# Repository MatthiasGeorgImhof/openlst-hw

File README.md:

$1K CubeSat Design
==========================

This forked repo adapts the hardware from the OpenLST Reference into something that works for my $1K CubeSat project

**Please note that this repository is desgined to be used as a submodule**, since it depends on symbols & footprints in my [1KCubeSat_Hardware repository](https://github.com/rgw3d/1KCubeSat_Hardware)

Overview
--------

This is an iteration on the OpenLST CC1110 based design, which itself is a simplified version of the TI CC1110 432 MHz reference design.
While the CC1110 can operate over 400-470MHz, this board is designed to operate around 435MHz, within the 435MHz-438MHz US Amateur radio band.
See the [FCC's chart, specifically section 5.282](https://transition.fcc.gov/oet/spectrum/table/fcctable.pdf)

* [Schematic](pdf/openlst-hw.pdf) in PDF form
* [Bill of materials](bom/) with ordering information & datasheet links
* [Gerber files](gerber/osh_park) for PCB fabrication

RF Pipeline
-----------

* **0433BM15A0001 Balun**. Designed for 430-435MHz, but should work up to 437MHz. Single part, designed specifically for the CC1110. I did not want to design my own balun.
* **PE4250MLI RF Switch**. Generic SPDT RF Switch. First RF switch breaks out to a test port. Second RF switch switches between TX & RX paths on the RF Frontend (RFFM6403).
* **RFFM6403 Analog Frontend**. TX path with 1.5W PA, RX path with LNA & SAW filter. Designed to work over the 408-455MHz band.
* **SF2446E SAW Filter**. Part of the Analog Frontend RX path. 430-440MHz band pass.
* 50 Ohm
* Impedance calculations for OSH Park PCB found [here](images/osh-park-4-layer-50ohms.png)

Pictures
--------

Original README below

OpenLST Reference Hardware
==========================

This repository contains a KiCad project with a hardware reference
implementation for the OpenLST.  This design is a simplified version
of the Texas Instruments CC1110 432 MHz reference design.  A 1 watt
power amplifier module has been added to increase operating range.
The design is intended for use at 437 MHz, however, it may be modified
for use at other frequencies.

The user is responsible for obtaining and maintaining the necessary
license to operate this radio.  The example project uses frequencies
in the US Amateur Radio UHF band. Transmissions in this band require a
valid FCC license and compliance with CFR Part 97.

License & Legal Information
---------------------------

Copyright 2018 Planet Labs Inc. This work is licensed under a
Creative Commons Attribution-ShareAlike 4.0 International License.

This document may contain technology or software the export of which
is or may be restricted by the Export Administration Act and the
Export Administration Regulations (EAR), 15 C.F.R. parts
730-774. Diversion contrary to U.S. law is prohibited.

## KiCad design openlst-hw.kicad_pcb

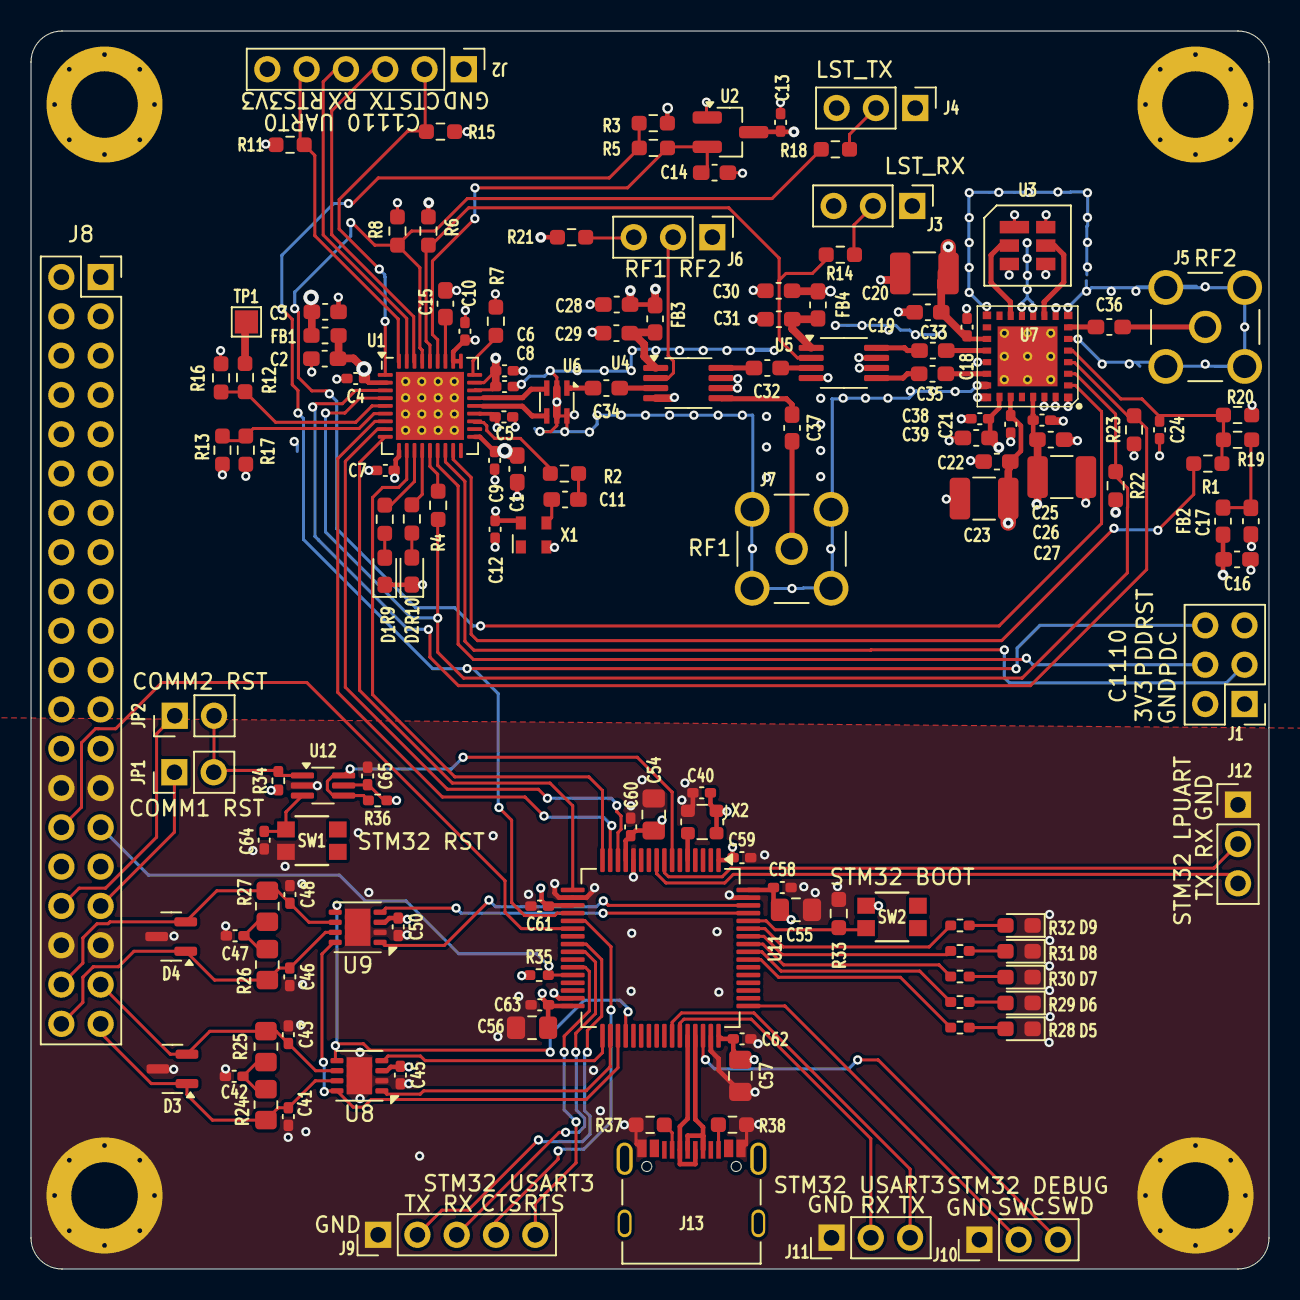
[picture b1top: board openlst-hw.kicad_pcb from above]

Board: 4 copper layers, 80.0 x 80.0 mm, 146 parts (0 on the bottom side), 104 nets.

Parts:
C1, C19, C22, C26, C39: 10u; C_0603_1608Metric_Pad1.08x0.95mm_HandSolder
C2, C3, C15, C16, C17, C28, C29, C30, C31: 1u; C_0603_1608Metric_Pad1.08x0.95mm_HandSolder
C4, C5, C6, C7, C8, C9, C10, C12, C13, C18, C21, C24, C25, C38, C40, C45, C50, C58, C59, C60, C61, C62, C63, C64, C65: 100n; C_0402_1005Metric_Pad0.74x0.62mm_HandSolder
C11, C14: 10n; C_0603_1608Metric_Pad1.08x0.95mm_HandSolder
C20, C23, C27: 47u; C_1210_3225Metric_Pad1.33x2.70mm_HandSolder
C32, C33, C34, C35, C36, C37: 220p; C_0603_1608Metric_Pad1.08x0.95mm_HandSolder
C41, C43, C46, C48: 100p; C_0402_1005Metric_Pad0.74x0.62mm_HandSolder
C42, C47: 4.7n; C_0402_1005Metric_Pad0.74x0.62mm_HandSolder
C54, C55, C56, C57: 10u; C_0805_2012Metric_Pad1.18x1.45mm_HandSolder
D1, D2: ORANGE; LED_0603_1608Metric_Pad1.05x0.95mm_HandSolder
D3, D4: NUP2105L; SOT-23
D5: LED_SMD_RED; LED_0603_1608Metric_Pad1.05x0.95mm_HandSolder
D6: LED_SMD_GREEN; LED_0603_1608Metric_Pad1.05x0.95mm_HandSolder
D7, D8, D9: LED_SMD_YELLOW; LED_0603_1608Metric_Pad1.05x0.95mm_HandSolder
FB1, FB2, FB3, FB4: Z=1k @ 100M; L_0603_1608Metric_Pad1.05x0.95mm_HandSolder
H1, H2, H3, H4: MountingHole_Pad; MountingHole_4.3mm_M4_Pad_Via_Custom
J1: CC Prog/Debug; PinHeader_2x03_P2.54mm_Vertical
J2: UART0; PinHeader_1x06_P2.54mm_Vertical
J3, J4: Control Outputs; PinHeader_1x03_P2.54mm_Vertical
J5: ANT; LINX_CONSMA001-G
J6: Switch Select; PinHeader_1x03_P2.54mm_Vertical
J7: Conn_Coaxial; LINX_CONSMA001-G
J8: PC104 Conn_02x20_Odd_Even; PinSocket_2x20_P2.54mm_Vertical
J9: Conn_01x05_Pin; PinHeader_1x05_P2.54mm_Vertical
J10, J11, J12: Conn_01x03_Pin; PinHeader_1x03_P2.54mm_Vertical
J13: 10155435-00011LF; AMPHENOL_10155435-00011LF
JP1, JP2: Jumper_2_Open; PinHeader_1x02_P2.54mm_Vertical
R1, R2, R4: 0; R_0603_1608Metric_Pad0.98x0.95mm_HandSolder
R3, R17: 47K; R_0603_1608Metric_Pad0.98x0.95mm_HandSolder
R5, R6, R8, R22, R23: 1K; R_0603_1608Metric_Pad0.98x0.95mm_HandSolder
R7: 56K; R_0603_1608Metric_Pad0.98x0.95mm_HandSolder
R9, R10: 680; R_0603_1608Metric_Pad0.98x0.95mm_HandSolder
R11, R15: 100K; R_0603_1608Metric_Pad0.98x0.95mm_HandSolder
R12, R16: DNP; R_0603_1608Metric_Pad0.98x0.95mm_HandSolder
R13, R21: 20K; R_0603_1608Metric_Pad0.98x0.95mm_HandSolder
R14, R18: 22; R_0603_1608Metric_Pad0.98x0.95mm_HandSolder
R19: 3.09K; R_0603_1608Metric_Pad0.98x0.95mm_HandSolder
R20: 6.65K; R_0603_1608Metric_Pad0.98x0.95mm_HandSolder
R24, R25, R26, R27: 60R4; R_0805_2012Metric_Pad1.20x1.40mm_HandSolder
R28, R29, R30, R31, R32: 680; R_0402_1005Metric_Pad0.72x0.64mm_HandSolder
R33: 10k; R_0603_1608Metric_Pad0.98x0.95mm_HandSolder
R34, R35, R36: 100K; R_0402_1005Metric_Pad0.72x0.64mm_HandSolder
R37, R38: 5K1; R_0603_1608Metric_Pad0.98x0.95mm_HandSolder
SW1, SW2: EVP-AA602W; EVP602AA
TP1: TestPoint; TestPoint_Pad_1.5x1.5mm
U1: CC1110; Texas_RHH0036C_VQFN-36-1EP_6x6mm_P0.5mm_EP4.4x4.4mm_Thermal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
U2: MIC803; SOT-23_Handsoldering
U3: SF2446E
U4, U5: PE4250MLI; MSOP-8_3x3mm_P0.65mm
U6: 0433BM15A0001; Balun_Johanson_0896BM15A0001
U7: RFFM6406
U8, U9: TCAN3414; VSON-8-1EP_3x3mm_P0.65mm_EP1.65x2.4mm
U11: STM32L496RGTx; LQFP-64_10x10mm_P0.5mm
U12: 74LVC2G07; SOT-363_SC-70-6_Handsoldering
X1: 27MHz; Oscillator_SMD_Abracon_ASDMB-4Pin_2.5x2.0mm
X2: 10MHz; Oscillator_SMD_ECS_2520MV-xxx-xx-4Pin_2.5x2.0mm

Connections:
/CAN Bridge/ATTENTION: J8.29, R35.2, U11.28 (PB2)
/CAN Bridge/CAN1_H: C46.1, D4.1 (K), J8.40, R26.1, U9.7 (CANH)
/CAN Bridge/CAN1_L: C48.2, D4.2 (K), J8.38, R27.2, U9.6 (CANL)
/CAN Bridge/CAN2_H: C41.1, D3.1 (K), J8.39, R24.1, U8.7 (CANH)
/CAN Bridge/CAN2_L: C43.2, D3.2 (K), J8.37, R25.2, U8.6 (CANL)
/CAN Bridge/CAN Transceiver1/CAN_RX: U9.4 (RXD), U11.61 (PB8)
/CAN Bridge/CAN Transceiver1/CAN_TX: U9.1 (TXD), U11.62 (PB9)
/CAN Bridge/CAN Transceiver1/SHDN: U8.5 (SHTD), U9.5 (SHTD), U11.36 (PB15)
/CAN Bridge/CAN Transceiver2/CAN_RX: U8.4 (RXD), U11.33 (PB12)
/CAN Bridge/CAN Transceiver2/CAN_TX: U8.1 (TXD), U11.34 (PB13)
/CAN Bridge/CAN_RS: U8.8 (STB), U9.8 (STB), U11.35 (PB14)
/CAN Bridge/COMM1_RST: J8.33, JP1.1 (A)
/CAN Bridge/COMM2_RST: J8.34, JP2.1 (A)
/CAN Bridge/EPS_RST: J8.30, U11.22 (PA6)
/CAN Bridge/PMIC/EXTR_RST: JP1.2 (B), JP2.2 (B), R34.2, U12.1 (IN1)
/CAN Bridge/PMIC/HSE_IN: U11.5 (PH0), X2.3 (OUTPUT)
/CAN Bridge/PMIC/LED1: R28.2, U11.55 (PB3)
/CAN Bridge/PMIC/LED2: R29.2, U11.56 (PB4)
/CAN Bridge/PMIC/LED3: R30.2, U11.57 (PB5)
/CAN Bridge/PMIC/LED4: R31.2, U11.58 (PB6)
/CAN Bridge/PMIC/LED5: R32.2, U11.59 (PB7)
/CAN Bridge/PMIC/LPUART_RX: J12.2, U11.8 (PC0)
/CAN Bridge/PMIC/LPUART_TX: J12.3, U11.9 (PC1)
/CAN Bridge/PMIC/SYS_JTMS_SWCLK: J10.2, U11.49 (PA14)
/CAN Bridge/PMIC/SYS_JTMS_SWDIO: J10.3, U11.46 (PA13)
/CAN Bridge/PMIC/Schmitt Trigger/IN2: C64.1, SW1.3, U12.3 (IN2)
/CAN Bridge/PMIC/Schmitt Trigger/OUT: R36.2, U11.7 (NRST), U12.4 (OUT2), U12.6 (OUT1)
/CAN Bridge/PMIC/USART1_RX: J11.2, U11.43 (PA10)
/CAN Bridge/PMIC/USART1_TX: J11.3, U11.42 (PA9)
/CAN Bridge/PMIC/USART3_CTS: J9.4, U11.21 (PA5)
/CAN Bridge/PMIC/USART3_RTS: J9.5, U11.27 (PB1)
/CAN Bridge/PMIC/USART3_RX: J9.3, U11.25 (PC5)
/CAN Bridge/PMIC/USART3_TX: J9.2, U11.24 (PC4)
/CAN Bridge/PMIC/USB/USB_OTG_FS_DM: J13.A7 (DN1_A), J13.B7 (DN2_B), U11.44 (PA11)
/CAN Bridge/PMIC/USB/USB_OTG_FS_DP: J13.A6 (DP1_A), J13.B6 (DP2_B), U11.45 (PA12)
/CAN Bridge/UART_CTS: U1.8 (P0_3), U11.14 (PA0)
/CAN Bridge/UART_RTS: U1.7 (P0_2), U11.15 (PA1)
/CAN Bridge/UART_RX: U1.9 (P0_4), U11.17 (PA3)
/CAN Bridge/UART_TX: U1.11 (P0_5), U11.16 (PA2)
/INTERBOARD_CONNECTOR2/3V3_17_RF1_BRIDGE: C40.1, C45.1, C50.1, C54.1, C55.1, C56.1, C57.1, C58.1, C59.1, C60.1, C61.1, C62.1, C63.1, C65.2, J8.23, R34.1, R35.1, R36.1, SW2.3, U8.3 (VCC), U9.3 (VCC), U11.1 (VBAT), U11.13 (VDDA), U11.19 (VDD), U11.32 (VDD), U11.48 (VDDUSB), U11.64 (VDD), U12.5 (VCC), X2.1 (TRI-STATE), X2.4 (VDD)
/INTERBOARD_CONNECTOR2/3V3_18_RF1_COMM: C3.1, C12.1, C13.2, C16.1, C28.1, C30.1, C38.1, C39.1, FB1.1, FB2.2, FB3.2, FB4.2, J1.2, J2.6, J3.3, J4.3, J8.24, R3.2, R6.2, R21.1, R22.2, U2.3 (VCC), U7.23 (VDD), X1.4 (Vcc)
/INTERBOARD_CONNECTOR2/BATT_1_COMM1_VRF: C18.1, C19.1, C20.1, C21.1, C22.1, C23.1, C25.1, C26.1, C27.1, J8.3, R13.2, U7.17 (VCC_RX), U7.24 (VCC_TX1), U7.26 (VCC_TX2)
/MCU/+3V3_C1110: C1.1, C2.1, C4.1, C5.1, C6.1, C7.1, C8.1, C9.1, C10.1, FB1.2, U1.2 (DVDD), U1.10 (DVDD), U1.19 (AVDD), U1.22 (AVDD), U1.25 (AVDD), U1.26 (AVDD), U1.28 (GUARD), U1.29 (AVDD_DREG)
/MCU/AN0: R12.1, R16.2, U1.5 (P0_0)
/MCU/AN1: R13.1, R17.2, U1.6 (P0_1)
/MCU/LST_RX_MODE: R6.1, R14.1, U1.32 (P1_7), U5.2 (V1)
/MCU/LST_TX_MODE: R8.2, R18.1, U1.33 (P1_6), U7.2 (TR)
/MCU/PA_VAPC: C24.1, R1.2, R19.2, R20.1, U7.5 (VAPC)
/MCU/RF_BYP: R23.2, U1.3 (P1_1), U7.4 (BYP)
/MCU/RF_EN: R4.2, R22.1, U1.4 (P1_0), U7.3 (EN)
/MCU/RF_N: U1.24 (RF_N), U6.3
/MCU/RF_P: U1.23 (RF_P), U6.4
/MCU/UART0_CTS: J2.2, R15.2, U1.1 (P1_2)
/MCU/UART0_RTS: J2.5, R11.2, U1.36 (P1_3)
/MCU/UART0_RX: J2.4, U1.35 (P1_4)
/MCU/UART0_TX: J2.3, U1.34 (P1_5)
GND: C1.2, C2.2, C3.2, C4.2, C5.2, C6.2, C7.2, C8.2, C9.2, C10.2, C12.2, C13.1, C14.1, C15.2, C16.2, C17.2, C18.2, C19.2, C20.2, C21.2, C22.2, C23.2, C24.2, C25.2, C26.2, C27.2, C28.2, C29.2, C30.2, C31.2, C38.2, C39.2, C40.2, C41.2, C42.2, C43.1, C45.2, C46.2, C47.2, C48.1, C50.2, C54.2, C55.2, C56.2, C57.2, C58.2, C59.2, C60.2, C61.2, C62.2, C63.2, C64.2, C65.1, D1.1 (K), D2.1 (K), D3.3 (A), D4.3 (A), D5.1 (K), D6.1 (K), D7.1 (K), D8.1 (K), D9.1 (K), H1.1, H2.1, H3.1, H4.1, J1.1, J2.1, J3.1, J4.1, J5.2 (Ext), J6.1, J7.2 (Ext), J8.1, J8.2, J8.27, J8.28, J8.35, J8.36, J9.1, J10.1, J11.1, J12.1, J13.A1_B12 (GND), J13.B1_A12 (GND__1), R7.1, R8.1, R11.1, R15.1, R16.1, R17.1, R20.2, R23.1, R33.2, R37.2, R38.1, SW1.4, U1.37 (GND_PAD), U2.1 (GND), U3.1 (GND), U3.3 (GND), U3.4 (GND), U3.6 (GND), U4.4 (GND), U4.6 (GND), U4.7 (GND), U5.4 (GND), U5.6 (GND), U5.7 (GND), U6.2 (GND), U6.5 (GND), U6.6 (GND), U7.1 (GND), U7.6 (GND), U7.8 (GND), U7.9 (GND), U7.11 (GND), U7.12 (GND), U7.15 (GND), U7.19 (GND), U7.21 (GND), U7.22 (GND), U7.27 (GND), U7.28 (GND), U7.29 (PAD), U8.2 (GND), U8.9 (GND), U9.2 (GND), U9.9 (GND), U11.12 (VSSA), U11.18 (VSS), U11.31 (VSS), U11.47 (VSS), U11.63 (VSS), U12.2 (GND), X1.2 (GND), X2.2 (GND)
LED1: R9.2, U1.12 (P0_6)
LED2: R10.2, U1.13 (P0_7)
LST_RESET: J1.6, R3.1, R5.2, U11.20 (PA4)
unnamed: C11.2, R2.2
unnamed: C17.1, FB2.1, R19.1
unnamed: C34.1, U6.1
unnamed: C42.1, R24.2, R25.1
unnamed: C47.1, R26.2, R27.1
unnamed: D1.2 (A), R9.1
unnamed: D2.2 (A), R10.1
unnamed: D5.2 (A), R28.1
unnamed: D6.2 (A), R29.1
unnamed: D7.2 (A), R30.1
unnamed: D8.2 (A), R31.1
unnamed: D9.2 (A), R32.1
unnamed: J3.2, R14.2
unnamed: J4.2, R18.2
unnamed: C36.2, J5.1 (In)
unnamed: J6.2, U4.2 (V1)
unnamed: J6.3, R21.2
unnamed: C37.2, J7.1 (In)
unnamed: J13.A5 (CC1_A), R37.1
unnamed: J13.B5 (CC2_B), R38.2
unnamed: R12.2, TP1.1
unnamed: C15.1, U1.30 (DCOUPL)
unnamed: R4.1, U1.14 (P2_0)
unnamed: R1.1, U1.17 (P2_3/XOSC32-1)
unnamed: R7.2, U1.27 (RBIAS)
unnamed: C14.2, R5.1, U1.31 (RESET_N), U2.2 (RESET)
unnamed: R2.1, U1.21 (XOSC-1)
unnamed: C37.1, U4.5 (RF1)
unnamed: C32.1, U4.8 (RF2)
unnamed: C34.2, U4.3 (RFC)
unnamed: C29.1, FB3.1, U4.1 (V2)
unnamed: C35.1, U5.5 (RF1)
unnamed: C33.1, U5.8 (RF2)
unnamed: C32.2, U5.3 (RFC)
unnamed: C31.1, FB4.1, U5.1 (V2)
unnamed: C36.1, U7.7 (ANT)
unnamed: C33.2, U7.18 (RX)
unnamed: U3.5 (RF), U7.10 (SAW1)
unnamed: U3.2 (RF), U7.13 (SAW2)
unnamed: C35.2, U7.20 (TX)
unnamed: R33.1, SW2.4, U11.60 (PH3_BOOT0)
unnamed: C11.1, X1.3 (OUT)
PROG_DC: J1.3, U1.16 (P2_2)
PROG_DD: J1.4, U1.15 (P2_1)

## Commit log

2021-08-30 Add new RF Frontend & other changes in progress
2021-10-17 Completed schematic, going to layout
2021-11-17 Radio board done, except for artwork touchup
2021-11-20 Final before gerbers are generated
2021-11-20 touchup fill missing via after reviewing gerbers
2021-11-20 Add Gerbers
2021-11-25 F Paste gerber
2022-01-03 Update README with test data
2024-08-18 upgrade to KICAD 8, change power converters and auxiliarry pin connectors
2024-08-18 change footprint to 80x80mm to fit cubesat 1U more comfortabley
2024-08-20 add CAN bridge, change bus connector from 2x20 to 2x24 to allow second can bus and battery
2024-08-21 cleanup, logical arrangement of connectors, short paths where possible and step files for all components
2024-08-24 break out RF part to separate schema, update BOM
2024-08-24 further refactor schema into subsheets
2024-08-25 automatic schematic and pcb valiadation and cleanup
2024-09-13 cleanup openlst board after connector update
2024-09-14 flip can high low around to ease access from front side
2024-09-23 temporary branch for radio to pc104
2024-09-24 use Common libraries, replace TI MCU with STM32 for CAN bridge
2024-09-24 integrated stm32 as CAN bridge and pc104 bus
2024-09-30 AVI light sensors with i2c multiplexers for AVI board. i2c amp/volt meter for attitude control coils
2024-10-02 openlst board to updated pc104 layout
2024-10-02 replacd TJA1042 with TCAN3414 that allows differential from 3V, negating the need for 5V generator
